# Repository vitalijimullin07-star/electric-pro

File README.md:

# Plata — редактор печатных плат в браузере

Полноценный редактор плат в духе EasyEDA: библиотека корпусов с реальными размерами, шаблоны плат, трассировка на одном или двух слоях, проверка правил на лету, автотрассировка, экспорт Gerber для завода и SVG 1:1 для домашнего ЛУТ. Работает на компьютере и телефоне, ничего не нужно устанавливать; проект хранится в браузере и в файле. Облако и учётные записи — следующий этап.

В папке `import/` — примеры для открытия через «Файл → Открыть файл проекта»: металлоискатель «Квазар AVR» (`quasar-avr-desalex.plata.json`) и пример симуляции Arduino (`arduino-simulation-demo.plata.json`).

## Что умеет

**Плата и компоненты**

- Один или два слоя меди, контур любой формы, скруглённые углы, вырезы, крепёжные отверстия.
- Библиотека из ~1040 корпусов, разложенных по разделам и подразделам (Резисторы → SMD чип / выводные / подстроечные…, Микросхемы → DIP / SOIC / TSSOP / QFP / QFN…):
  - **Резисторы**: чипы 0201…2512, сборки 4×0603, осевые 0,125–5 Вт лежа и стоя, цементные, SIP-сборки, подстроечные Bourns 3362/3386/3296 и RM-065, переменные WH148/RK09, терморезисторы NTC, фоторезисторы.
  - **Конденсаторы**: керамика 0201…2220, тантал A–E, алюминиевые SMD 4…16 мм, электролиты Ø4…30, дисковые, плёночные и X2 до 27,5 мм, ионисторы, триммеры.
  - **Индуктивности**: чипы, силовые CD32…CD105 и экранированные, осевые, радиальные, тороиды.
  - **Диоды и светодиоды**: SOD-123/323/523, SMA/SMB/SMC, MELF, DO-35/41/15/27/201, P600, мосты KBP/KBU/GBU/KBPC/DB107/MBS; LED 0603…1206, PLCC-2/4/6, WS2812B, 3/5/8/10 мм, RGB, двухцветные.
  - **Транзисторы**: SOT-23/323/523/563/363/89/223, DPAK, D2PAK, PowerPAK, TO-92 (3 варианта), TO-18/39, TO-126, IPAK, TO-220 (вертикально, лежа, 2 и 5 выводов), TO-247, TO-264, TO-218, TO-3.
  - **Микросхемы**: DIP-4…64 на 7,62 / 10,16 / 15,24 / 22,86 мм и панельки, SOIC узкие и широкие, SOP EIAJ, TSSOP-8…48, SSOP, QSOP, MSOP, SOT-23-8, TQFP/LQFP 32…144, QFN-16…64 с площадкой, DFN, оптроны DIP/SOP-4/SOIC, стабилизаторы TO-92/TO-220.
  - **Разъёмы**: штыри 1×1…40 и 2×1…40, гнёзда, угловые, шаг 2,0 и 1,27 мм, IDC 2×3…2×32, JST XH/PH/SH/VH, Molex KK, клеммники 3,5/3,81/5,0/5,08/7,5/10,16 мм и разъёмные, DC-005, USB-A/Micro-B/Type-C, 3,5 мм, RJ45/RJ11, держатели CR2032/18650/AA/AAA, ножевые контакты.
  - **Кнопки и переключатели**: тактовые 3×4…12×12 (TH и SMD), сенсорные площадки, ползунковые, DIP-переключатели, энкодеры EC11/EC12, микропереключатели, тумблер, клавиша, Cherry MX и Kailh Choc.
  - **Дисплеи и индикаторы**: семисегментные 0,36″…1″ на 1–4 разряда, матрицы 8×8, шкала, зуммеры TH/SMD, пьезо, динамики, микрофоны.
  - **Кварцы**: 2016/2520/3225/5032/7050, часовые 3215/2012, HC-49S/U, цилиндры, генераторы DIP и SMD, керамические и ПАВ-резонаторы.
  - **Реле, датчики, питание, защита**: SRD, HK4100F, G5LE, G5V-1/2, ТТР; DS18B20, LM35, DHT11, SHT3x, BME280, MPX5100, MQ-x, ACS712, ZMCT103C, ZMPT101B, Холла, геркон, PIR, HC-SR04; HLK-PM01/5M05, IRM-05, DC-DC SIP, K7805; предохранители SMD/TH/PTC, варисторы, разрядники, TVS.
  - **Крепёж и технологическое**: отверстия M2…M5 с кольцом и без, паз, контрольные точки, площадки под провод, паяные перемычки, реперные знаки.
  - **Модули** (~60): ESP32 DevKit 30/38, ESP32-S3, ESP32-C3 SuperMini, ESP32-CAM, ESP-12F, ESP-01, NodeMCU, D1 mini, nRF24L01, HC-05, RFM95, SIM800L, Arduino Nano/Pro Mini/Micro, Pro Micro, Digispark, XIAO, Teensy 4.0, Pico, RP2040-Zero, Blue/Black Pill, TP4056, MP1584, XL4015, MT3608, LM2596, A4988, TB6612, L298N, IRF520, D4184, реле 1/2/4 канала, PCA9685, MPU6050, BMP280, INA219, ACS712, PIR, RC522, джойстик, microSD, RTC, LCD1602/2004, OLED 0,91/0,96/1,3″, Nokia 5110, TFT 1,8/2,4″, TM1637, MAX7219, кольцо WS2812.
- У каждого корпуса пометка: размеры сверены со стандартом или типовые (проверить по даташиту). Совместимые корпуса можно менять одним щелчком (SMD ↔ выводной).
- Модули для Arduino — больше 200: весь набор датчиков KY, платки GY (BME280, BH1750, MPU, ADXL345…), газовые MQ-2…MQ-135, дальномеры, HX711, драйверы моторов, реле, радио (HC-12, 433 МГц, RS-485, CAN), дисплеи, звук (DFPlayer, MAX98357A), питание, контур шилда Arduino Uno R3. Порядок выводов — как у типовых платок, помечены «сверить».
- Микросхемы и транзисторы с распиновкой по даташиту: ATmega328P, ATtiny85/84/2313, ATmega16/32, PIC, CH340G, NE555/556, LM358/324/339/741/386, 74HC595/165/00/04/138, CD4051/4017, ULN2003/2803, L293D, MAX232/485, MCP2515, DS1307, 24Cxx, PCF8574, MCP23017, MCP3008, HX711, оптроны, стабилизаторы 7805/LM317/AMS1117, транзисторы и симисторы в TO-92/TO-220/SOT-23.
- Распиновка на шелкографии: у каждого вывода с именем (GND, SDA, D13, OUT…) подпись снаружи от площадки — видна и после пайки модуля или микросхемы. При шаге выводов меньше 1 мм подписи только на сборочном слое.
- Шаблоны: пустые платы ходовых размеров, плата под ЛУТ, еврокарта, шилд Arduino Uno с отверстиями по чертежу, Raspberry Pi HAT, плата под Pi Pico, корпус на DIN-рейку.
- Перетаскивание, поворот, перенос на другую сторону, рамка выделения, стрелки для точного сдвига, отмена и повтор.
- Копировать, вырезать, вставить под курсор, дублировать; выравнивание и распределение, группы (Ctrl+G), размерные линии.
- Дорожки тянутся за компонентом: при переносе и повороте концы на его площадках едут следом с изломом 45° (выключается в меню «Упорядочить» — тогда к оторванным выводам видны воздушные линии).
- Перенос между слоями: F переносит выделенные дорожки, полигоны и графику на слой другой стороны; окно «Перенос между слоями» переносит всё со слоя на слой или меняет два слоя местами. На стыках с дорожками прежнего слоя ставятся переходные.
- Массовая замена корпусов: все резисторы, конденсаторы, транзисторы или детали одного корпуса — разом или выборочно; из библиотеки — «Заменить им детали на плате».
- Перо (S Pen и другие): точный захват, прицел при наведении, ладонь на экране не мешает, кнопка на пере — сдвиг вида или свойства, ластик стирает, долгое нажатие — свойства.
- Графика: максимальная (полная чёткость экрана, свечение, блики на меди, анимация выделения), сбалансированная, экономная; «Авто» подбирает по устройству и снижает качество, если кадры рисуются медленно.
- Редактор корпусов: ряды, двухрядные и четырёхсторонние раскладки площадок, контур и габарит автоматически; свои корпуса хранятся в разделе «Мои корпуса» и выгружаются файлом.
- Импорт KiCad: корпуса `.kicad_mod` и целые платы `.kicad_pcb` (детали, дорожки, переходные, полигоны, контур).
- Импорт Sprint Layout 5 и 6 (`.lay`, `.lay6`): медь, площадки, полигоны, шелкография и надписи, контур (слой O или тонкая рамка вокруг платы). Группы с площадками становятся деталями со своими корпусами, одиночные площадки — переходными, цепи восстанавливаются по связности меди.
- 3D-вид платы: вращение, вид сверху и снизу, высоты корпусов типовые.

**Схема**

- Отдельный лист принципиальной схемы: символы строятся по категории детали, провода, метки цепей и питания.
- «Обновить плату по схеме» переносит цепи на плату; «Добавить на схему детали с платы» — обратно. Печать схемы в PDF.

**Цепи и трассировка**

- Цепи назначаются выводам в свойствах компонента; классы цепей задают зазор, ширину дорожки и размер переходного. Класс «Сеть 230 В» с зазором 6 мм до всего остального и область правил «Зона 230 В».
- Ручная трассировка с изгибами 45°, автоширина по классу, переходные отверстия с переходом на другой слой (V), перемычки проводом для односторонних плат, воздушные линии до ближайшего островка цепи.
- Проверка правил на лету: зазоры между цепями с учётом классов, замыкания, неразведённые цепи, край платы, минимальные ширины и отверстия, кольца, расстояние между отверстиями, запретные области и области только для своих классов, перекрытие габаритов, висящие дорожки.
- Автотрассировка методом согласования конфликтов: дорожки прямо и под 45°, один слой с перемычками или два с переходными, учитывает классы, области правил и зону 230 В; после согласования — чистовой проход (убирает лишние перемычки и обходы). Можно развести всё или только недоведённые цепи. Цепи, которые соединяет полигон, не разводятся дорожками, к полигону ставятся переходные.
- Авторасстановка компонентов (галочка «Расставить»): меньше пересечений связей и связей через ряды выводов, выводы 230 В — в своей зоне с зазором до логики, помехоопасные — подальше от чувствительных, разъёмы — к краю, конденсаторы развязки — к выводам питания; закреплённые детали остаются на месте.
- Ширина дорожек по токам: ток выводов берётся из деталей (AMS1117 — 1 А, AP63205 — 2 А, HLK-PM01 — 0,6 А, предохранитель — по номиналу, трансформатор — по ВА, двигатель — по мощности, ESP32 — пики радио), ширина — по IPC-2221 (толщина меди и допустимый нагрев — в правилах). Галочка «авто» у ширины: дорожка сразу нужной ширины, у тонких выводов и чужой меди сама сужается; «Трассировка → Ширина дорожек по токам» расширяет уже проведённые; ток цепи можно задать вручную в её свойствах.
- Роли цепей галочками: сеть 230 В (класс Mains, зазор 6 мм), питание и силовые (шире), помехоопасные (ШИМ, ключи, кварц, тактовые) и чувствительные (аналог, датчики, АЦП) — угадываются по классам, именам и деталям, любую роль можно поменять.
- Распутанная паутина: воздушные линии каждой цепи выбираются так, чтобы меньше пересекаться друг с другом и не идти сквозь ряды выводов; число пересечений — в строке над платой. Расстановка доводит места деталей по распутанной паутине, трассировка может идти по её плану.
- Разводка по этапам: цепи 230 В с большим зазором — на своей крупной сетке, остальное — на мелкой, кратной шагу выводов; у модулей и микросхем с шагом 1,27 мм дорожки ведутся тонко и потом расширяются до ширины класса и тока, где хватает места. Каждый вариант укладывается в выбранное время.
- Перебор вариантов на всех ядрах (воркер на ядро): каждый вариант — своё семя расстановки и своя стратегия трассировки; 15 с — 5 мин; лучшие — карточками с миниатюрой и оценкой по паутине («около N перемычек»), любой применяется в одно касание (и отменяется Ctrl+Z). Для односторонней платы можно заодно посмотреть двусторонний вариант.
- Полигоны меди: заливка с зазорами до чужих цепей, термобарьеры, удаление островов; во время перетаскивания заливка не пересчитывается.
- Каплевидные переходы от дорожек к площадкам и переходным.
- Проверка для производства (Файл → Проверка для производства): замеры зазоров, дорожек, отверстий, поясков, шелкографии и маски под выбранное производство — типовой завод, классы точности 3–5 по ГОСТ Р 53429 или домашний ЛУТ; параметры для формы заказа и список свёрл.

**Симуляция с прошивкой**

- Arduino Uno, Nano, Pro Mini и ATmega328P выполняют настоящую прошивку (.hex из Arduino IDE: «Скетч → Экспорт бинарного файла») прямо в браузере — эмулятор avr8js, 16 МГц, таймеры, ШИМ, UART, АЦП, I²C, SPI.
- ATmega32A/ATmega16A (DIP-40, порты A–D): свои регистры таймеров, разностные каналы АЦП с усилением, EEPROM; частота — по кварцу на схеме (11,0592 МГц, 8 МГц…). Если AREF соединён с питанием, опора АЦП — это напряжение.
- Схема считается по номиналам: делители напряжения из резисторов, аккумулятор с ползунком напряжения, диоды (клавиатуры на диодах), кнопки между сигнальными линиями, транзисторные ключи NPN/PNP и полевые, дроссели как перемычки по постоянному току, выводы, которые «держит» питание сильнее выхода.
- Детали берутся со схемы или платы: светодиоды светятся (с яркостью по ШИМ), кнопки нажимаются касанием на плате или схеме, потенциометры и датчики — ползунками, зуммер звучит.
- Поддерживаются: ЖК 1602/2004 (по I²C через PCF8574 и параллельно), OLED SSD1306/SH1106, часы DS3231/DS1307, АЦП ADS1115, DHT11/DHT22, HC-SR04, MAX6675/MAX31855, реле; выходы остальных модулей — ползунками и переключателями.
- Монитор порта (приём и отправка), таблица выводов с уровнями и ШИМ, логический анализатор. Замыкание выхода с другим источником и «висящие» входы отмечаются.
- Пример: `import/arduino-simulation-demo.plata.json` — откройте и нажмите «Симуляция → Старт».
- Металлоискатель «Квазар AVR» (Andy_F, плата DesAlex): `import/quasar-avr-desalex.plata.json` — плата из Sprint Layout, полная схема, прошивка 1.4.5. Работают самотест портов, меню и шесть кнопок, дисплей со шкалой VDI, звук, подсветка; катушка DD — модель с выбором металла и глубины, кнопка «Провести над целью». Памятка по сборке и проводам — `import/quasar-avr-desalex.txt`.
- «Симуляция → Во весь экран»: экраны, энкодер и кнопки крупно, список деталей и монитор порта. На телефоне — сверху; «Назад» закрывает.
- Аналоговый расчёт (галочка «аналоговый расчёт» на вкладке «Симуляция», включён по умолчанию): вся схема считается как в EveryCircuit/LTspice — узловой метод, шаг 0,5–10 мкс (по умолчанию 2 мкс), кусочно-линейные модели в «идеальных условиях»: резисторы (с тепловым шумом у входов усилителей), конденсаторы, дроссели, диоды, светодиоды, стабилитроны, MOSFET (порог, сопротивление канала, паразитный диод, ёмкость затвора), биполярные транзисторы (отсечка/усиление/насыщение), ОУ и компараторы (усиление, полоса, упор в питание, шум), TL431, линейные стабилизаторы, таймер 555, двигатель постоянного тока (ЭДС, момент, инерция), кнопки, аккумулятор, динамик, выводы контроллера. Контроллер работает как раньше, его АЦП и внешний АЦП читают напряжения из расчёта.
  - Вкладка «Цепь»: деталь (касанием на плате или из списка) — ползунки номинала и параметров прямо на ходу, показания (напряжение, ток, мощность, режим транзистора, нагрев стабилизатора), «В проект» — записать номинал в деталь; осциллограф на 4 канала (напряжения цепей, токи выводов) с синхронизацией по фронту; АЧХ от любой цепи до напряжения или тока детали.
  - На плате дорожки и площадки окрашены по напряжению (синий — 0 В, красный — наибольшее), ток бежит жёлтыми точками по направлению тока (быстрее — больше ток); на схеме выводы окрашены по напряжению, кольцо — ток через вывод.
  - «Квазар»: катушка DD — три связанные индуктивности (TX 0,8 мГн, RX 11,4 мГн, цель — виток с постоянной времени вихревых токов), сведение (остаточная связь TX→RX в ppm), L и R обмоток — ползунками. Передатчик на IRF840/IRF9640 даёт 8,2 кГц и ~240 мА, прошивка в меню «Coil balance» показывает разбаланс, «TX frequency» — частоту и ток. Металлы разносятся по фазе физически (фольга → золото → никель → медь → серебро), железо попадает в маску. Фаза феррита зависит от настройки приёмного контура, в прошивке её подстраивает «Ferrite calibr.».
  - Ограничения: без температуры, разброса и паразитных ёмкостей монтажа (это следующий шаг — физическое положение деталей); расчёт в 2–4 раза медленнее реального времени на плате вроде «Квазара» (шаг 2 мкс), при шаге 1 мкс — ещё вдвое.
- Симуляция без контроллера: если на схеме нет Arduino или ATmega, «Старт» запускает только аналоговый расчёт — прошивка не нужна. Схема включается с нуля, как при подаче питания; кнопки держатся, пока нажаты, тумблеры переключаются касанием (в панели или на плате), светодиоды, лампы, зуммеры, реле и двигатели — карточками. Время — реальное или замедленное/ускоренное (от 0,001× до 100×).
  - Питание: аккумулятор или батарея (по обозначению GB/BT), клеммник с моделью «источник питания», сеть 230 В 50 Гц по цепям L и N, генераторы на вкладке «Цепь» (постоянное, синус, меандр, треугольник, сеть — на любую цепь, сохраняются в проекте). Цепи с именами VCC, +5V, +12V питаются сами, только если к ним не подходит ни один источник.
  - Параметры на ходу прямо на плате или схеме: тройной щелчок или удержание (пальцем, пером, мышью) на детали во время симуляции — карточка у детали: ползунки всех параметров модели (у резистора — сопротивление и допустимая мощность, у конденсатора — ёмкость и номинальное напряжение, у диода — прямое напряжение, сопротивление и обратный пробой, у транзистора — β, U бэ, насыщение и пробой коллектор—эмиттер, у MOSFET — порог, сопротивление канала, ёмкость затвора и пробой, у источника — напряжение и ток ограничения…), точное значение вводом («4,7к», «100н», «2.2u»), шаги ◀ ▶ по ряду E24, ↺ — вернуть исходное; показания (ток, напряжение, мощность, перегрузка) обновляются на ходу. На дорожке, проводе или метке — напряжение цепи, её источники с ползунками и детали на ней (касание — перейти к детали). Карточку можно тащить за заголовок; касание другой детали переводит её туда; Esc, ✕ или «Назад» — закрыть. Двойной щелчок во время симуляции открывает окно детали с небольшой задержкой (ждёт третьего).
  - Модель каждой детали — в свойствах, раздел «Модель для симуляции»: «авто» (по обозначению, номиналу и корпусу) или вручную из списка, с параметрами (напряжение, ток, КПД, порог…); «не участвует в расчёте» — убрать деталь, например, диод на катушке реле, и увидеть выброс. Параметры, поменянные ползунками на ходу, «В проект» записывает туда же.
  - Модели: резистор, потенциометр, NTC, фоторезистор, конденсатор (электролит — с полярностью), дроссель, предохранитель (сгорает по току), перемычка; диод, светодиод, стабилитрон, диодный мост, MOSFET N/P (с пробоем сток—исток), транзисторы n-p-n/p-n-p (с пробоем коллектор—эмиттер), симистор, тиристор; ОУ, компаратор, TL431, таймер 555, логика 74HC/CD40 (вентили И-НЕ, ИЛИ-НЕ, И, ИЛИ, исключающее ИЛИ, инверторы, триггеры Шмитта, счётчик CD4017, регистр 74HC595), драйвер L293D (вперёд, назад, торможение), ключи ULN2003/2803; оптрон с транзистором (PC817), оптосимистор (MOC30xx, с переходом через ноль у MOC306x), быстрый оптрон 6N137, реле (катушка с индуктивностью и ёмкостью витков, срабатывание и отпускание с гистерезисом, контакты NO/NC); трансформатор, линейный стабилизатор (78xx, LM317, AMS1117), DC-DC (понижающий и повышающий «в среднем», с КПД); нагрузка, лампа накаливания, динамик, зуммер, двигатель постоянного тока; кнопка, выключатель, переключатель, микропереключатель, DIP-переключатель; датчик тока ACS712, датчик Холла (цифровой A3144 и аналоговый SS49E), датчик температуры LM35/TMP36, ЖК-модуль (подсветка и потребление), катушка металлоискателя.
  - Примеры: «Файл → Новый проект → Примеры» — мигалка на NE555, блок питания 12 В от сети (трансформатор, мост, 7812, предохранитель), ШИМ-регулятор двигателя, реле с кнопкой, бегущие огни на CD4017. Детали расставлены, цепи заданы, плата не разведена.
  - Ограничения: модели кусочно-линейные и «в среднем» (DC-DC — без пульсаций переключения, двигатель — без пульсаций коллектора); у логики нет задержек распространения; сеть относительно земли схемы «плавает» (развязана трансформатором или оптроном), поэтому напряжения на L и N по отдельности условны — смотрите разность.
- Выносные детали (дисплей, кнопки на корпусе, динамик, датчик) отмечаются в свойствах «выносная (вне платы)»: они есть на схеме, в перечне и в симуляции, но не на плате и не в Gerber.

**Экспорт**

- На завод: Gerber RS-274X с атрибутами X2 (медь, маска, шелкография, паста, контур), сверловка Excellon (PTH и NPTH), перечень элементов и файл расстановки — одним архивом.
- В архив для завода кладётся отчёт проверки для производства с параметрами заказа.
- Дома: PDF для ЛУТ строго 1:1 на A4 или A3 (несколько копий на лист, зеркало, негатив, линейка 50 мм), медь в SVG 1:1 (точки под кернение), сборочный вид, список соединений, комплект архивом.
- Проект в JSON (самодостаточный: корпуса внутри), недавние проекты в браузере.
- Установка как приложение (PWA): после первого открытия редактор работает без интернета.

## Как открыть

**В браузере:** https://vitalijimullin07-star.github.io/electric-pro/ — GitHub Pages публикует корень ветки `main`, где лежит собранный редактор (`index.html`).

**Одним файлом:** `npm run build` собирает `dist/plata.html` — его можно открыть двойным щелчком без интернета.

**Для разработки:**

```
npm install
npm run dev          # откроется http://localhost:5173/app.html
npm run build        # сборка: dist/ и корневой index.html для сайта
```

После изменений кода запустите `npm run build` и закоммитьте обновлённый `index.html` — CI проверяет, что сайт собран из текущих исходников.

## Как пользоваться

1. **Файл → Новый проект**: выберите шаблон или задайте размер, число слоёв и правила (завод или ЛУТ).
2. **Библиотека** (вкладка справа или клавиша P): найдите корпус, «Поставить на плату», щёлкните по плате. R — поворот, Esc — закончить.
3. **Двойной щелчок по компоненту**: обозначение, номинал, замена корпуса, назначение цепей выводам (новое имя создаёт цепь).
4. **Дорожка (W)**: щелчок по площадке — начало, щелчки ставят изгибы, щелчок по площадке той же цепи заканчивает. V — переходное и смена слоя, Backspace — убрать изгиб, `/` — тип изгиба.
5. **Трассировка → Автотрассировка и расстановка**: галочки — расставить, развести, что учитывать; сколько искать; выбрать вариант из найденных.
6. **Проверка** (вкладка справа): список замечаний, щелчок ведёт к месту на плате.
7. **Файл → Проверка для производства**: выберите завод или ЛУТ, исправьте замечания, скопируйте параметры в форму заказа.
8. **Файл → Экспорт**: архив Gerber для завода или PDF 1:1 для ЛУТ.
9. **Схема** (переключатель вверху слева): поставьте детали из библиотеки, соедините проводами (W) и метками (N), затем «Обновить плату по схеме».
10. **Сохранить** (Ctrl+S или значок дискеты): проект сохраняется в память устройства, без окна скачивания. Список — значок папки или «Файл → Мои проекты на устройстве»: открыть, переименовать, скачать файлом, удалить. Открытые файлы `.plata.json` попадают в список сами. Файл для передачи — «Файл → Скачать файл проекта».

Кнопка «Назад» (Android, жест назад) закрывает меню, окно, панель, начатое действие, инструмент, выделение, возвращает со схемы на плату; когда закрывать нечего — второе нажатие в течение 2,5 с выходит из редактора.

Горячие клавиши — в меню «Справка».

## Структура

```
index.html, src/app/            точка входа и раскладка
src/core/math/                  векторы, отрезки, многоугольники, фигуры (капсулы, скруглённые прямоугольники), пространственный индекс
src/core/model/                 модель проекта, слои, правила и классы цепей, размещение корпусов, геометрия в координатах платы,
                                связность и воздушные линии, проверка правил (DRC), операции редактирования
src/core/library/               библиотека корпусов (генераторы SMD, выводных, модулей), шаблоны плат
src/core/router/                автотрассировка и её воркер
src/core/io/                    Gerber/Excellon, SVG, PDF (ЛУТ и схема), BOM и расстановка, файл проекта, архивы, импорт KiCad, Sprint Layout и старого формата
src/core/render/                штриховой шрифт, развёртка проекта в примитивы по слоям, сцена 3D-вида
src/core/schematic/             символы, список цепей схемы, перенос на плату
src/core/fab/                   проверка для производства (DFM) и параметры заказа
src/core/examples/              сборка проекта «Квазар» из файла Sprint Layout, примеры схем без контроллера (sim-circuits.ts)
src/core/sim/analog/            аналоговый расчёт: разреженное LU, движок (θ-метод), элементы (elements.ts, elements-ext.ts), виды деталей
                                и ручной выбор (kinds.ts), модели деталей (models.ts), сборка из проекта (build.ts), карточки (devices.ts), катушка DD
src/core/sim/                   симуляция: AVR (ATmega328P, ATmega32A), цепи и уровни, детали,
                                ЖК, OLED, катушка металлоискателя, аналоговый расчёт
import/                         файлы для открытия в редакторе: пример Arduino, «Квазар AVR»
src/editor/                     состояние редактора (zustand + immer), история, команды, обработка мыши и касаний,
                                «Мои проекты» в памяти устройства (IndexedDB, device-files.ts)
src/render/                     отрисовка на Canvas и проверка попадания курсора
src/ui/                         React: меню, панель инструментов, холст, панели, диалоги, стили, кнопка «Назад» (back-button.ts)
tests/                          vitest: библиотека, «Квазар», автотрассировка, экспорт
tools/e2e.mjs                   сквозной прогон интерфейса в Chromium (Playwright), запускается вручную
```

Ядро не зависит от React и DOM: работает в воркере и в Node, поэтому автотрассировка и экспорт покрыты тестами.

## Формат проекта

Все размеры в миллиметрах, ось Y вниз. Проект — один JSON: метаданные, плата (контур, слои, толщина), правила, классы цепей, цепи, копии используемых корпусов, компоненты (положение, поворот, сторона, вывод → цепь), дорожки (ломаные с шириной и слоем), переходные, перемычки, полигоны, области правил, графика. Версия формата хранится в поле `version`; старые файлы дополняются при открытии.

## Проверки

```
npm run typecheck    типы
npm test             тесты: библиотека, образец платы (связность и DRC), автотрассировка с нуля, экспорт
npm run check        всё вместе
npm run e2e          сквозной прогон интерфейса (нужен собранный dist и Chromium из Playwright)
```

## Что дальше

- Облако: учётные записи, проекты онлайн, совместная работа.
- Дуги в дорожках, тонкая подгонка дорожек.
- Перестановка выводов и вентилей при трассировке (другой вывод контроллера, другой вентиль микросхемы) — только отдельной галочкой: меняет схему и прошивку.
- Пазы (сейчас выгружаются круглыми отверстиями), экспорт в KiCad, многолистовая схема.
- Больше модулей и корпусов со сверенными размерами; принимаются измерения реальных деталей.

Перед травлением или заказом распечатайте сборочный вид 1:1 и приложите детали к бумаге: корпуса с пометкой «размеры типовые» стоит сверить с даташитом.

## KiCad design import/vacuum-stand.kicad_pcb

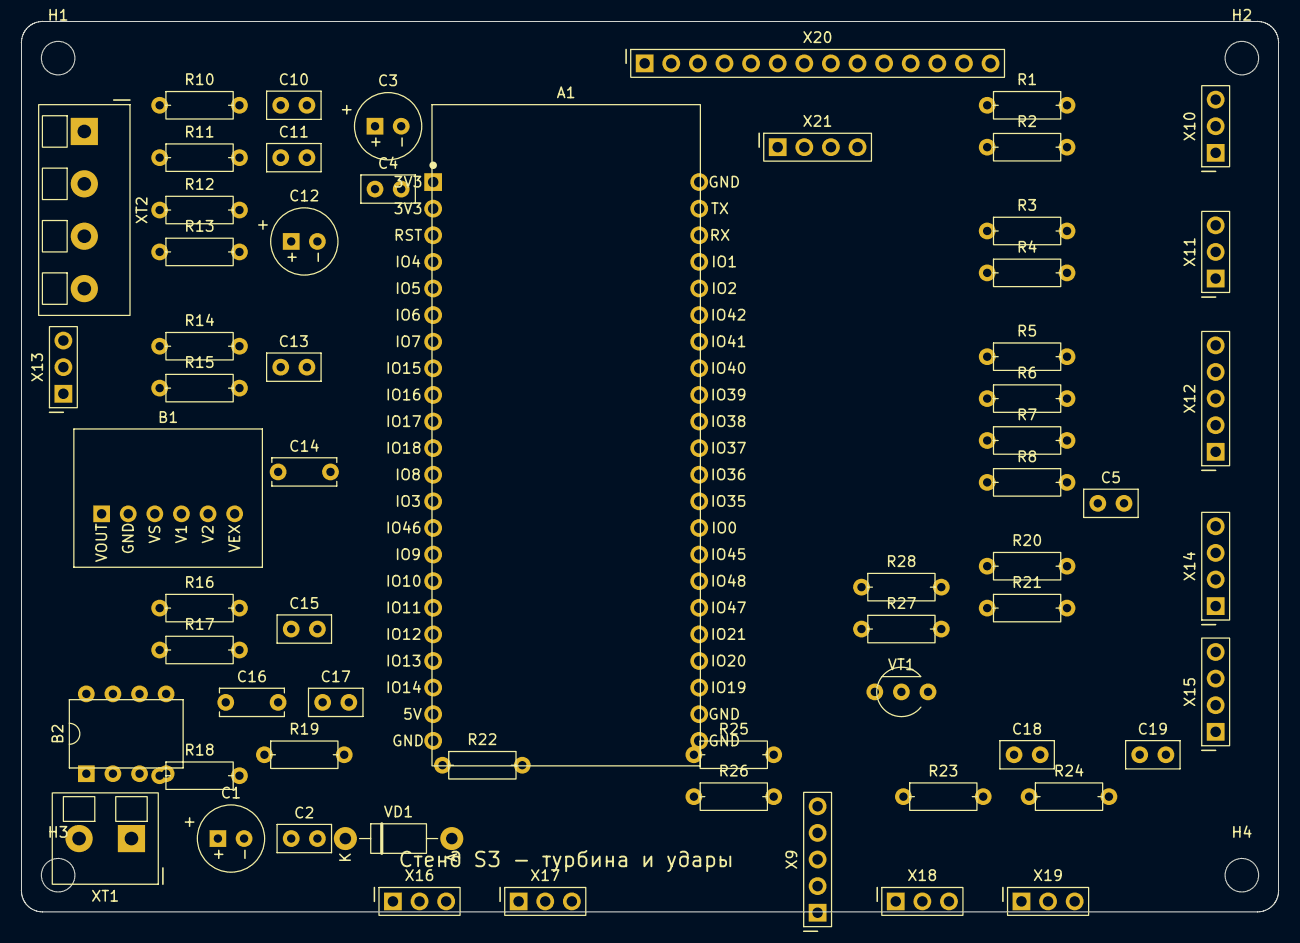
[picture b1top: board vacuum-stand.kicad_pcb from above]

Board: 2 copper layers, 120.0 x 85.0 mm, 66 parts (0 on the bottom side), 44 nets, no tracks yet.

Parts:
A1: ESP32-S3-DevKitC-1 N16R8; Module_ESP32-S3_DevKitC-1
B1: MPX5100DP; Sensor_MPX5100DP
B2: MPXV7007DP; DIP-8_W7.62mm_Socket
C1: 470 мкФ 10 В; CP_Radial_D6.3mm_P2.5mm
C2, C4: 100 нФ; C_Disc_D5mm_W2.5mm_P2.5mm
C3, C12: 10 мкФ; CP_Radial_D6.3mm_P2.5mm
C5, C13, C18, C19: 1 нФ; C_Disc_D5mm_W2.5mm_P2.5mm
C10, C11, C15, C17: 10 нФ; C_Disc_D5mm_W2.5mm_P2.5mm
C14, C16: 1 мкФ; C_Disc_D6mm_W2.5mm_P5mm
H1, H2, H3, H4: MountingHole_3.2mm_M3
R1, R3, R5, R7: 100; R_Axial_0.25W_L6.3mm_D2.5mm_P7.62mm_Horizontal
R2, R4, R6, R8, R12, R13, R14, R17, R19, R23, R24, R25, R26, R28: 10k; R_Axial_0.25W_L6.3mm_D2.5mm_P7.62mm_Horizontal
R10, R11, R27: 1k; R_Axial_0.25W_L6.3mm_D2.5mm_P7.62mm_Horizontal
R15: 20k; R_Axial_0.25W_L6.3mm_D2.5mm_P7.62mm_Horizontal
R16, R18: 6,8k; R_Axial_0.25W_L6.3mm_D2.5mm_P7.62mm_Horizontal
R20, R21, R22: 4,7k; R_Axial_0.25W_L6.3mm_D2.5mm_P7.62mm_Horizontal
VD1: 1N5819; D_DO-41_P10.16mm_Horizontal
VT1: S8550; Q_S8050_TO-92_Wide
X9: Запас; PinHeader_1x05_P2.54mm
X10: МР248 турбины 1; PinHeader_1x03_P2.54mm
X11: МР248 турбины 2; PinHeader_1x03_P2.54mm
X12: Диммер 2 канала; PinHeader_1x05_P2.54mm
X13: ZMPT101B; PinHeader_1x03_P2.54mm
X14: TCA9548A; PinHeader_1x04_P2.54mm
X15: BME280; PinHeader_1x04_P2.54mm
X16: DS18B20 №1; PinHeader_1x03_P2.54mm
X17: DS18B20 №2; PinHeader_1x03_P2.54mm
X18: Холл 1; PinHeader_1x03_P2.54mm
X19: Холл 2; PinHeader_1x03_P2.54mm
X20: Экран ILI9488; PinHeader_1x14_P2.54mm
X21: Карта экрана; PinHeader_1x04_P2.54mm
XT1: 5 В; TerminalBlock_1x02_P5mm
XT2: ТТ1, ТТ2; TerminalBlock_1x04_P5mm

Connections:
3V3: A1.1 (3V3), A1.2 (3V3), C3.1 (+), C4.1, R12.1, R20.2, R21.2, R22.2, R23.2, R24.2, R25.2, R26.2, R28.2, VT1.1 (E), X9.4, X10.1, X11.1, X12.1, X14.1, X15.1, X16.1, X17.1
5V: B1.3 (VS), B2.2, C1.1 (+), C2.1, C14.1, C16.1, VD1.2 (A), X13.1, X18.1, X19.1, X20.1, XT1.1
5V_ESP: A1.21 (5V), VD1.1 (K)
BL_B: R27.2, R28.1, VT1.2 (B)
CT1: A1.4 (IO4), C10.1, R10.2
CT1_IN: R10.1, XT2.1
CT2: A1.5 (IO5), C11.1, R11.2
CT2_IN: R11.1, XT2.3
DIM1: R5.2, R6.1, X12.4
DIM2: R7.2, R8.1, X12.5
DPF: A1.6 (IO6), C17.1, R18.2, R19.1
DPF_S: B2.4, R18.1
GND: A1.22 (GND), A1.23 (GND), A1.24 (GND), A1.44 (GND), B1.2 (GND), B2.3, C1.2 (-), C2.2, C3.2 (-), C4.2, C5.2, C10.2, C11.2, C12.2 (-), C13.2, C14.2, C15.2, C16.2, C17.2, C18.2, C19.2, R2.2, R4.2, R6.2, R8.2, R13.2, R15.2, R17.2, R19.2, X9.5, X10.2, X11.2, X12.2, X13.3, X14.2, X15.2, X16.3, X17.3, X18.3, X19.3, X20.2, XT1.2
HALL1: A1.13 (IO3), C18.1, R23.1, X18.2
HALL2: A1.15 (IO9), C19.1, R24.1, X19.2
LCD_BL: A1.39 (IO42), R27.1
LCD_CS: A1.43 (TX), X20.3
LCD_DC: A1.11 (IO18), X20.5
LCD_LED: VT1.3 (C), X20.8
LCD_RST: A1.27 (IO21), R25.1, X20.4
OW: A1.7 (IO7), R22.1, X16.2, X17.2
PWM1: R1.2, R2.1, X10.3
PWM2: R3.2, R4.1, X11.3
SCL: A1.18 (IO12), R21.1, X14.3, X15.3
SDA: A1.17 (IO11), R20.1, X14.4, X15.4
SD_CS: A1.20 (IO14), R26.1, X21.1
SPARE1: A1.41 (IO1), X9.1
SPARE2: A1.40 (IO2), X9.2
SPARE3: A1.19 (IO13), X9.3
SPI_MISO: A1.10 (IO17), X20.13, X21.3
SPI_MOSI: A1.9 (IO16), X20.6, X20.12, X21.2
SPI_SCK: A1.8 (IO15), X20.7, X20.10, X21.4
T1: A1.36 (IO39), R1.1
T2: A1.35 (IO38), R3.1
T_CS: A1.31 (IO0), X20.11
T_IRQ: A1.28 (IO47), X20.14
UAC: A1.12 (IO8), C13.1, R14.2, R15.1
UAC_IN: R14.1, X13.2
VAC: A1.16 (IO10), C15.1, R16.2, R17.1
VAC_S: B1.1 (VOUT), R16.1
VLV1: A1.37 (IO40), R5.1
VLV2: A1.38 (IO41), R7.1
VMID: C12.1 (+), R12.2, R13.1, XT2.2, XT2.4
ZC: A1.29 (IO48), C5.1, X12.3

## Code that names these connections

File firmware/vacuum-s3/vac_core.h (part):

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#define PIN_RL1 1       /* модуль реле турбины 1 (K1) */
#define PIN_RL2 2       /* модуль реле турбины 2 (K2) */
#define PIN_RL3 42      /* модуль реле розетки инструмента (K3) */
#define PIN_VLV2 41     /* SSR клапана 2 (CH2) */
#define PIN_VLV1 40     /* SSR клапана 1 (CH1) */
#define PIN_T1 39       /* ШИМ регулятора МР248 турбины 1 (100 Ом, 10 кОм к земле) */
#define PIN_T2 38       /* ШИМ регулятора МР248 турбины 2 */
#define PWM_HZ 20000    /* ШИМ МР248: его вход сглаживает, мощность — по среднему напряжению */
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#define PIN_NTC2 8
/* Навесной монтаж (6.1): на IO7 — ZMPT101B через делитель 10к/20к (напряжение сети), термисторы — на
 * АЦП ADS1115. Что на IO7, прошивка видит сама: переменное 50 Гц — ZMPT, постоянное — термистор. */
#define PIN_UAC 7
#define PIN_WL1 3       /* электрод уровня E1 (делитель 100к/100к) */
#define PIN_WL_DRV 46   /* раскачка электродов: меандр → 1 кОм → 1 мкФ → E0 */
#define PIN_WL2 9       /* электрод перелива E2 */
#define PIN_VAC 10      /* разрежение MPX5100DP через делитель 6,8к/10к */
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#define PIN_SCL 12
#define PIN_PNL_TX 13   /* UART1 → плата экрана (если экран отдельной платой), без неё — голос DFPlayer 9600 */
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#define PIN_ZC 48       /* ноль сети: детектор на плате (импульс «1» у нуля) или ZMPT101B (меандр) — узнаёт сам */
#define PIN_BUZZER 45   /* ключ зуммера (база через 1 кОм) */
/* Экран ILI9488 и касание XPT2046 на общей шине SPI (их ведёт vacuum-s3.ino, не ядро). */
#define PIN_SPI_SCK 15
#define PIN_SPI_MOSI 16
#define PIN_SPI_MISO 17 /* только от касания: выход экрана SDO не подключён */
#define PIN_LCD_DC 18
#define PIN_LCD_CS 43   /* вывод TX платы (UART0 загрузчика: при работе свободен) */
#define PIN_TOUCH_CS 0  /* вывод BOOT: при загрузке подтянут вверх — касание не выбрано */

#define SDP_FILTER 0x25 /* SDP810-500Pa: перепад на фильтре */
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
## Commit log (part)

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2026-05-19 Clean modular Electric Pro
2026-05-19 Upload clean modular Electric Pro
2026-05-19 Add assets and config folders
2026-05-19 Upload hybrid Electric Pro
2026-05-21 Wipe repository before new modular build
2026-05-21 Upload modular visual shell v1
2026-05-21 Connect Firebase config
2026-05-21 Make mobile visual more compact
2026-05-21 Add cache busting and app version check
2026-05-21 Remember Firebase login
2026-05-21 Upload visual editor v2
2026-05-21 Clean full rebuild v4
2026-05-21 Final visual v5 clean rebuild
2026-05-21 Fix visual settings toggles on mobile
2026-05-21 Fix visual buttons switches and sounds
2026-05-21 Use real visual toggles and more soft sounds
2026-05-21 Fix sound unlock after reload
2026-05-21 Fix diagnostics formatting and refresh session log
2026-05-21 Setup Firebase foundation and admin bootstrap
2026-05-21 Add admin panel users management
2026-05-21 Add protected AI balance and device integrity foundation
2026-05-21 Add admin user card with AI balance
2026-05-21 Add subscription and YooKassa foundation
2026-05-21 Add subscription UI for admin and masters
2026-05-21 Fix Firebase Functions SDK loading
2026-05-21 Improve subscription AI notice readability
2026-05-21 Improve security policy toggles
2026-05-21 Improve admin subscription period buttons
2026-05-21 Force security toggles and improve admin readability
2026-05-21 Clean admin card and remove overlay patches
2026-05-21 Fix security toggle visual layout
2026-05-21 Fix missing SubscriptionAPI methods
2026-05-21 Add mini subscription status to header
2026-05-21 Fix subscription access alias and header mini status layout
2026-05-21 Move subscription status to top of app
2026-05-21 Fix subscription request payment alias
2026-05-21 Final clean admin subscription AI security UI
2026-05-21 Add subscription access gate
2026-05-21 Add server protected access gate limits
2026-05-21 Redesign admin subscription management
2026-05-21 Finalize strict subscription access and admin panel fixed
2026-05-21 Fix admin panel Firestore permissions
2026-05-21 Fix subscription status card
2026-05-21 Hide duplicate subscription status block
2026-05-21 Stop freeze and scope subscription status safely
2026-05-21 Fix admin event journal and subscription duplicate
2026-05-21 Make admin event journal clickable
2026-05-21 Fix admin logs layout and refresh behavior
2026-05-21 Hide current access duplicate on subscription page
2026-05-21 Render admin journal as diagnostics
2026-05-21 Add log TTL cleanup and error highlight
2026-05-21 Fix Android back button navigation
2026-05-21 Create V20 clean stable base
2026-05-21 Fix admin logs internal function error
2026-05-21 Fix admin subscription controls UI
2026-05-22 Add Pool V21 base module
2026-05-22 Add module version badges
2026-05-22 Improve pool frame UI
2026-05-22 Fix pool controls and compact frame UI
2026-05-22 Fix pool controls and add ceiling height
2026-05-22 Stabilize pool controls V21.7
2026-05-22 Hide temporary extra pool fields V21.8
2026-05-22 Add pool keys and logic editor V21.9
2026-05-22 Compact pool logic editor V21.10
2026-05-22 Fix pool logic editor button V21.11
2026-05-22 Fix pool logic editor input focus V21.12
2026-05-22 Hard reset pool UI V21.13
2026-05-22 Replace pool input fields with prompt edit tiles V21.14
2026-05-22 Add pool connector templates V21.15
2026-05-22 Add universal connector math V21.16
2026-05-22 Force connector draft output V21.17
2026-05-22 Show visible connector lines V21.18
2026-05-22 Add auth auto restore V21.19
2026-05-22 Sync pool version badge V21.20
2026-05-22 Hard fix pool build connectors V21.21
2026-05-22 Replace pool patches with clean V22 monolith
2026-05-22 Fix pool V22 route and auth log spam V22.1
2026-05-22 Hard clean legacy pool patches V22.2
2026-05-25 Force pool route to V22.2
2026-05-25 Connect pool V22.2 force route
2026-05-25 Fix Android back and add home menu V22.3
2026-05-25 Add pool DB picker V22.4
2026-05-25 Make pool DB picker safer V22.5
2026-05-25 Force safe pool DB picker V22.5.1
2026-05-25 Add manual DB candidate picker V22.6
2026-05-25 Fix pool V22.6 version lock V22.6.1
2026-05-25 Guard pool version after delete V22.6.2
2026-05-25 Build stable pool monolith V22.7
2026-05-25 Add estimate core foundation V23.1
2026-05-25 Improve database UI folders and cards V24.2
2026-05-25 Fix database V24.2 UI version display
2026-05-25 Rebuild database as file manager V24.3
2026-05-25 Fix database card modal actions V24.3.1
2026-05-25 Fix database menu duplicates and diagnostics toolbar V24.3.2
2026-05-25 Improve database import and autosave V24.3.3
2026-05-25 Build database clean monolith V24.4
2026-05-26 Fix database UI server sync and masters V24.4.1
2026-05-26 Add database diagnostics dot V24.4.3
2026-05-26 Show database version and header diagnostics dot V24.4.4
2026-05-26 Lock database visible version V24.4.5
2026-05-26 Build hard app shell and burger menu monolith V24.5
2026-05-26 Build hard database monolith V25
2026-05-27 Clean database leaks from main screen V25.3
2026-05-27 Fix copy path for old burger visual package V25.4.2
2026-05-27 Prevent database auto-open and unlock burger V25.5
2026-05-27 Rollback shell and burger to stable V24.3.2
2026-05-27 Fix database burger badge and safe monolith open V25.6
2026-05-27 Force database modal style V25.7
2026-05-27 Full rollback before database monolith V24.3.3
2026-05-27 Add surgical monolith database V26.0
2026-05-27 Route database menu to V26 monolith V26.1
2026-05-27 Fix database interactions V26.2
2026-05-27 Lock visible DB version V26.2.1
2026-05-27 Fix visible DB version V26.2.2
2026-05-27 Finish database interactions V26.3
2026-05-27 Finish database smart sort edit import V26.4
2026-05-28 Hard lock database route to V26.4.1
2026-05-28 Fix database V26.4.2 modal CSS installer
2026-05-28 Add Firebase sync for database V26.5
2026-05-28 Fix access UI duplicate and subscription balance pull V26.6.1
2026-05-28 Restore admin subscription panel V26.7
2026-05-28 V26.8 DB hard clear
2026-05-28 V26.9 top status lock
2026-05-28 V26.10 DB cloud sync
2026-05-28 V26.11 DB diagnostics safe
2026-05-28 V26.12 Pool zero switch reset
2026-05-28 V26.15 main DB picker estimate
2026-05-28 V26.16 status main route fix
2026-05-28 V26.17.1 active base picker fix
2026-05-28 V27.1 DB clean bridge
2026-05-28 V27.2 main picker route guard
2026-05-28 V27.3 active base lock
2026-05-31 V27.4 Clean DB header: single Firebase status bar, version label fix
2026-05-31 V27.5 One DB status bar: merged sync + access status into single compact bar
2026-05-31 V27.6 Compact picker: smaller cards + editable quantity field
2026-05-31 V27.7 Picker folders: collapsible folders/subfolders like DB screen
2026-05-31 V27.8 Excel import: parse .xlsx in-browser via SheetJS, reuse preview pipeline
2026-05-31 V27.9 File-manager picker: clean nested folder navigation
2026-06-01 V27.10 compact cards in folders + scroll position fix
2026-06-01 V28.2 Shield configurator screens (clean module)
2026-06-01 V28.2.1 Shield configurator full screens (settings, profile, room hints, draft, actions)
2026-06-01 V28.2.2 Shield UI: collapse-by-default, smaller non-overlapping action buttons
2026-06-01 V28.3.1 Resolver hardened for real supplier names (verified vs invoices)
2026-06-01 V28.5 DB structured params: auto-recognize specs for all items + DB button; resolver uses specs
2026-06-01 V28.5.1 Shield: keep settings open on change + tap draft line to replace breaker from DB
2026-06-02 V28.3b-1 Shield: 5 protection groups with group RCD/diff + per-line breakers from DB
2026-06-02 V28.3b-2 Shield options: collapsible Options under settings + protection apparatus + distribution/rules
2026-06-02 V28.3b-3 Shield: consumables/buses by formula + priced from DB; grand total
2026-06-02 V28.3b-3.1 Shield: PuGV section choice + NSHVI pairing + comb sum + brief apparatus summary
2026-06-02 V28.4-1 Shield rail layout: visual DIN-rail packing 12 modules/row from draft
2026-06-02 V28.4-2 Shield rail: under Options, fullscreen, labeled devices (QF/QD) + tap-for-card
2026-06-02 V28.4-3 Shield: collapse/expand group lines via group header chevron
2026-06-02 V28.4-5 Shield: SVG single-line scheme (from scheme.html engine) auto-built from configurator
2026-06-02 V28.4-6 Shield scheme: GOST 2.755-style contact-based UGO symbols
2026-06-02 V28.4-7 Shield scheme: inline symbols with explicit fill/stroke (fix black toroid)
2026-06-02 V28.5-perf: debounce badges + access-UI boot-once/lighter observer/capped retries/warn logs
2026-06-02 V28.7 DB Currency and Money Precision
2026-06-03 V28.6 Currency: global EPCurrency + DB selector + kopeck formatting
2026-06-03 V28.7 Currency app-wide + no rounding (DB/shield/estimate via EPCurrency, kopecks)
2026-06-03 V28.8 Shield fixes1: sizes, niche x modules, mount rename, class label, fullscreen btn
2026-06-03 V28.8.1 HOTFIX: define module-level cur() so shield configurator opens
2026-06-03 V28.9 Shield: all protection apparatus in draft/rail/scheme + summary incl. not-found 10mA
2026-06-03 V28.9.1 Shield: master button auto-adds contactor placed in lighting branch (scheme+rail)
2026-06-03 V28.11 Shield: low-current shield toggle + module count -> materials
2026-06-03 V28.12 Shield: custom template editor (save/apply/delete) in Шаблоны
2026-06-04 V28.6 Safety Fix: rules privilege-escalation + structure, periodDays/trial, admin via Cloud Functions
2026-06-04 V28.13 Shield: print PDF + save PNG for rails and scheme (offline SVG export)
2026-06-04 V28.14 Manual single-line builder -> configurator (manual mode compute)
2026-06-04 V28.15 Cable in manual builder + aggregate to materials/estimate (shared cable module)
2026-06-04 V28.16 Ship scheme engine with node.cable -> cable visible on single-line
2026-06-04 V28.17 Manual single-line: per-line curve, brand+add, zoom; engine text halo fix
2026-06-04 V28.18 Manual single-line: apparatus on group/line + count to materials
2026-06-04 V28.19 Phase pole slashes (1ф/3ф) on single-line + per group/line phase selection
2026-06-05 V28.20 Diff curve selector + visible line curve/amp + fullscreen-schematic pinch zoom
2026-06-05 V28.21 Compact group/line rows + phase-aware cable (1ф=3 жилы, 3ф=4/5 жил)
2026-06-05 V28.22 RCD type (AC/A/B) selector + remove inline labels; type feeds DB match
2026-06-05 V28.23 Compact group parameter rows (no full-width selects)
2026-06-05 V28.24 Size tune: smaller input/brand selects, compact group params (фит в 2 строки)
2026-06-05 V28.26 GOST: move cable label lower (wire segment to load)
2026-06-08 V28.27 Input apparatus click-order + reorder + input feed cable (incl ПуГВ)
2026-06-08 V28.28 Group apparatus before/after УЗО + reorder ◀▶ + count after-apps in BOM
2026-06-08 V28.29 Inter-apparatus cable segments drawn + ОБВЯЗКА (ПуГВ) note; finish order/segment styling
2026-06-08 V28.30 Drag-to-reorder chips (Pointer Events) for input/group/line apparatus
2026-06-08 V28.31 Auth Perf Safe: fix auth.js - guard for loadProfileOrCreate, defer seedAdminMeta, use requestAnimationFrame for showApp
2026-06-08 V28.31 Auth Perf Safe: remove setInterval loops, remove global click listener, add restoreExecuted guard
2026-06-08 V28.31 Auth Perf Safe Firebase: fix seedAdminMeta to not overwrite sync_versions, add global lock, add firestore timeout
2026-06-09 V28.31 Canvas block drag (move mode ✥ + reset ⟲) on GOST schematic
2026-06-09 V28.32 Semi-transparent up/down reorder buttons on GOST schematic for input apparatus
2026-06-09 V28.33 Reorder buttons (input/group/line) with form sync; remove block finger-drag
2026-06-09 V28.34 Vertical reorder buttons on group/line apparatus (До/После УЗО, line apps) with form sync
2026-06-09 V28.35 Configurator scheme uses GOST view with group/line apparatus; renderer interactive flag
2026-06-09 Cleanup: remove dead JS/CSS, backups, changelog docs from deploy (V28.35)
2026-06-09 V28.36 Router fix: pool exit uses Router.load('main') instead of nonexistent 'home' route
2026-06-09 V28.37 Router: normalize unknown/alias routes to main in load() (fixes currentRoute mislabel)
2026-06-09 V28.38 DB: consolidate editor + 2 patches into one monolith; drop orphan database-api.js
